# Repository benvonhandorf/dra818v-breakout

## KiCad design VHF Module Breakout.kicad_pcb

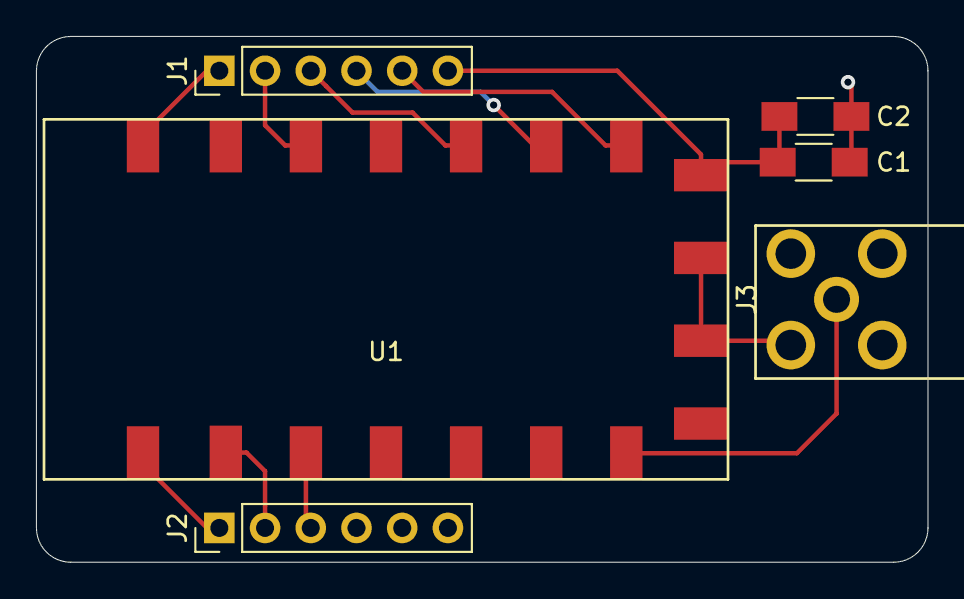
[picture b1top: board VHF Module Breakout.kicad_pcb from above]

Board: 2 copper layers, 49.5 x 29.2 mm, 6 parts (0 on the bottom side), 11 nets.

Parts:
C1: 1uF; C_1206_HandSoldering
C2: 10uF; C_1206_HandSoldering
J1, J2: Conn_01x06_Male; Pin_Header_Straight_1x06_Pitch2.54mm
J3: Conn_Coaxial; SMA_THT_90deg
U1: DRV818V

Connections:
GND: C1.2, C2.2, J2.5, J2.6, J3.2, U1.9, U1.10
unnamed: C1.1, C2.1, J1.6, U1.8
unnamed: J1.1, U1.1
unnamed: J1.2, U1.3
unnamed: J1.3, U1.5
unnamed: J1.4, U1.6
unnamed: J1.5, U1.7
unnamed: J2.1, U1.18
unnamed: J2.2, U1.17
unnamed: J2.3, U1.16
unnamed: J3.1, U1.12

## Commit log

2022-07-02 Backup
